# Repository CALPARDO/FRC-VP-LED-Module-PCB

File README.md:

# What is this?
This is an LED Module for retroreflective tapes in FRC with 10mm LEDs and 150Ω resistors on 5V. Use 5V 500mA pins on VRM.

# 3D View

# 3D View Top

# Top

# Bottom

# Usage

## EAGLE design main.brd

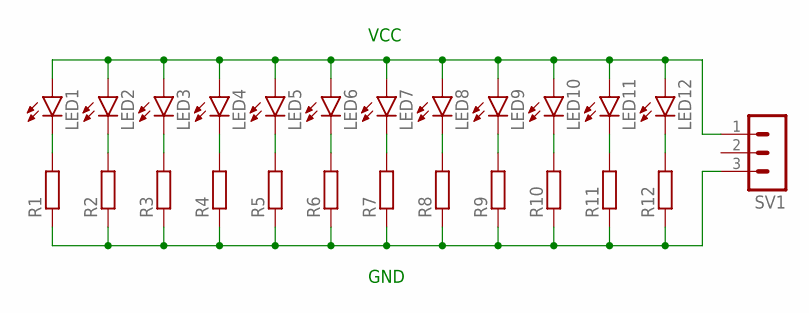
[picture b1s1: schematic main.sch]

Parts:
LED1, LED2, LED3, LED4, LED5, LED6, LED7, LED8, LED9, LED10, LED11, LED12: LED10MM
R1, R2, R3, R4, R5, R6, R7, R8, R9, R10, R11, R12: R-EU_0204/7; 0204/7
SV1: MA03-1

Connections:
GND: R1.1, R2.1, R3.1, R4.1, R5.1, R6.1, R7.1, R8.1, R9.1, R10.1, R11.1, R12.1, SV1.3
unnamed: LED1.K (C), R1.2
unnamed: LED2.K (C), R2.2
unnamed: LED3.K (C), R3.2
unnamed: LED4.K (C), R4.2
unnamed: LED5.K (C), R5.2
unnamed: LED6.K (C), R6.2
unnamed: LED7.K (C), R7.2
unnamed: LED8.K (C), R8.2
unnamed: LED9.K (C), R9.2
unnamed: LED10.K (C), R10.2
unnamed: LED11.K (C), R11.2
unnamed: LED12.K (C), R12.2
VCC: LED1.A, LED2.A, LED3.A, LED4.A, LED5.A, LED6.A, LED7.A, LED8.A, LED9.A, LED10.A, LED11.A, LED12.A, SV1.1

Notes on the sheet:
GND
VCC

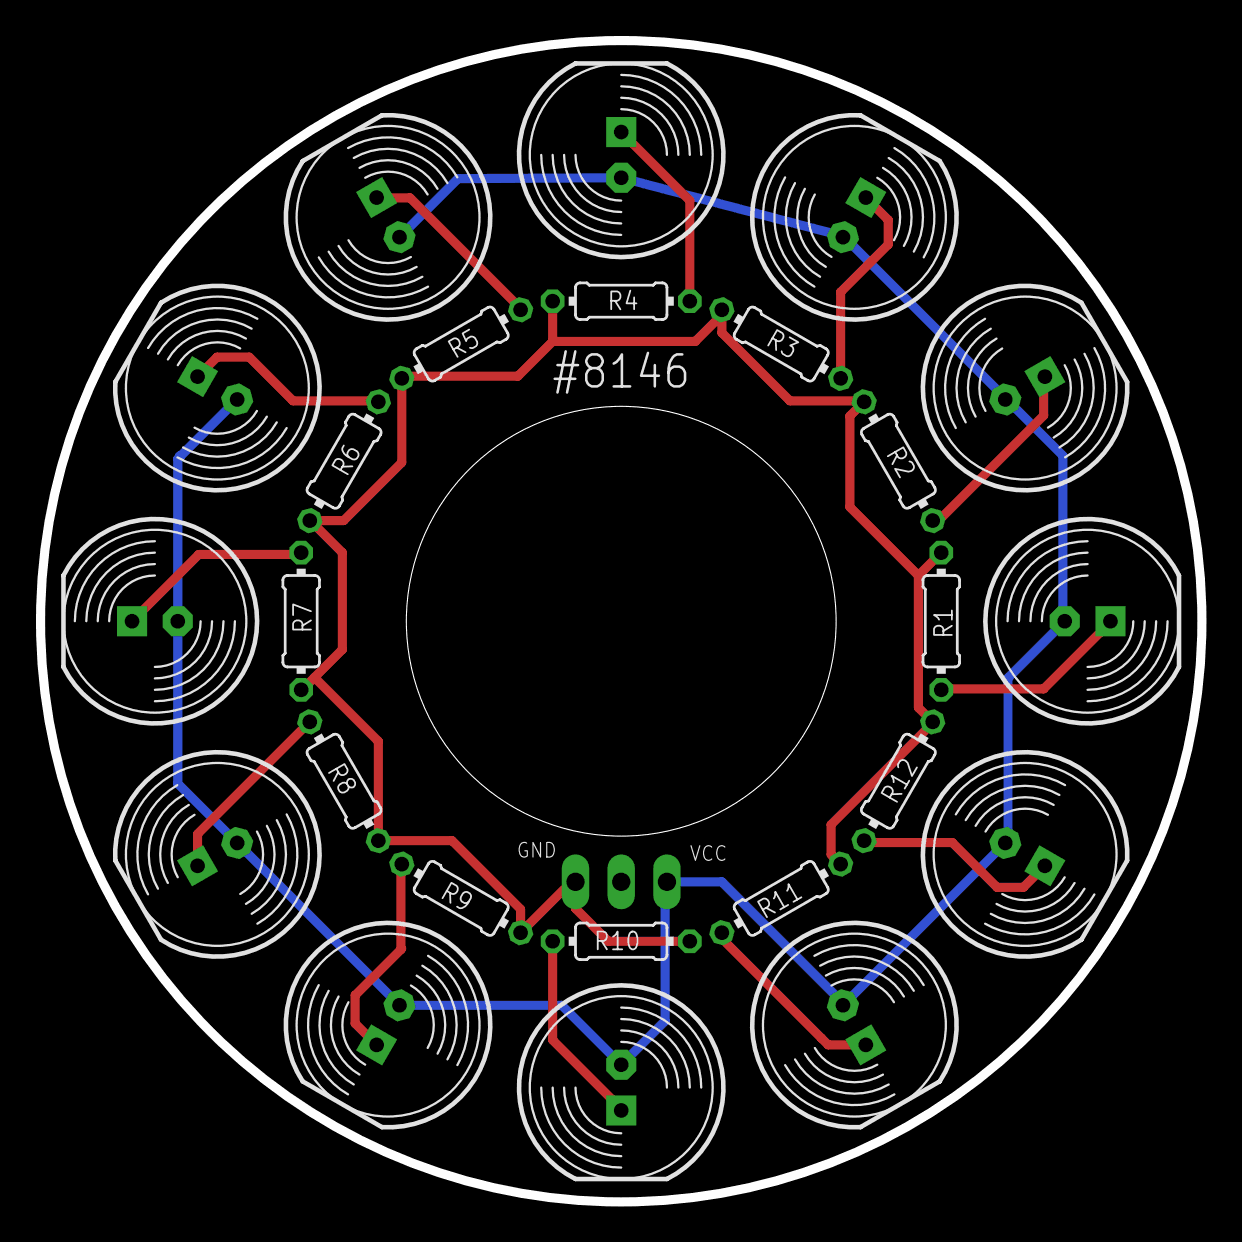
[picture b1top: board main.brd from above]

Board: 2 copper layers, 64.5 x 64.5 mm, 25 parts (1 on the bottom side), 14 nets.
